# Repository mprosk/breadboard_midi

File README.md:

# MIDI Breadboard Adapter
MIDI breakout board for prototyping on a breadboard. Easily communicate with digital instruments from an Arduino or other microcontroller. Includes all hardware required to drive the MIDI current loop from a UART.

## Voltage Compatibility

The breakout board can be configured to work with both 3.3V and 5V microcontrollers. Since MIDI uses current, not voltage to encode bits, the values of the current limiting resistors can be changed to reflect the different voltage level. The list of resistor values for each voltage mode is shown below.

| Resistor | 5V Bus | 3.3V Bus |
| -------- | ------ | -------- |
| R1       | 280    | 180      |
| R2       | 220    | 220      |
| R3       | 220    | 10       |
| R4       | 220    | 33       |

## MIDI Pass Through

The adapter can also be configured to pass the MIDI IN data that it receives directly to the MIDI OUT stream, allowing your microcontroller to passively monitor the MIDI link between two other MIDI devices. Useful for debugging or for splitting the upstream data to both your project and another MIDI endpoint.

To enable this option, simply connect a jumper between the IN and OUT pins on the breadboard adapter.

## Bill of Materials

| Quantity | Line Item                                          |
| -------- | -------------------------------------------------- |
| 1        | 6N138 optoisolator                                 |
| 1        | 8DIP socket                                        |
| 1        | 1N914 signal diode                                 |
| 2        | 5-pin 180' DIN socket                              |
| 3        | 0.1uF capacitors                                   |
| 1        | 74LVCG125 buffer gate                              |
| 16       | 0.1" pitch male pin headers (4x 2-unit, 2x 4-unit) |

#### 5V Configuration

| Quantity | Line Item         |
| -------- | ----------------- |
| 3        | 220 ohm resistors |
| 1        | 280 ohm resistor  |

#### 3.3V Configuration

| Quantity | Line Item        |
| -------- | ---------------- |
| 1        | 10 ohm resistor  |
| 1        | 33 ohm resistor  |
| 1        | 220 ohm resistor |
| 1        | 280 ohm resistor |

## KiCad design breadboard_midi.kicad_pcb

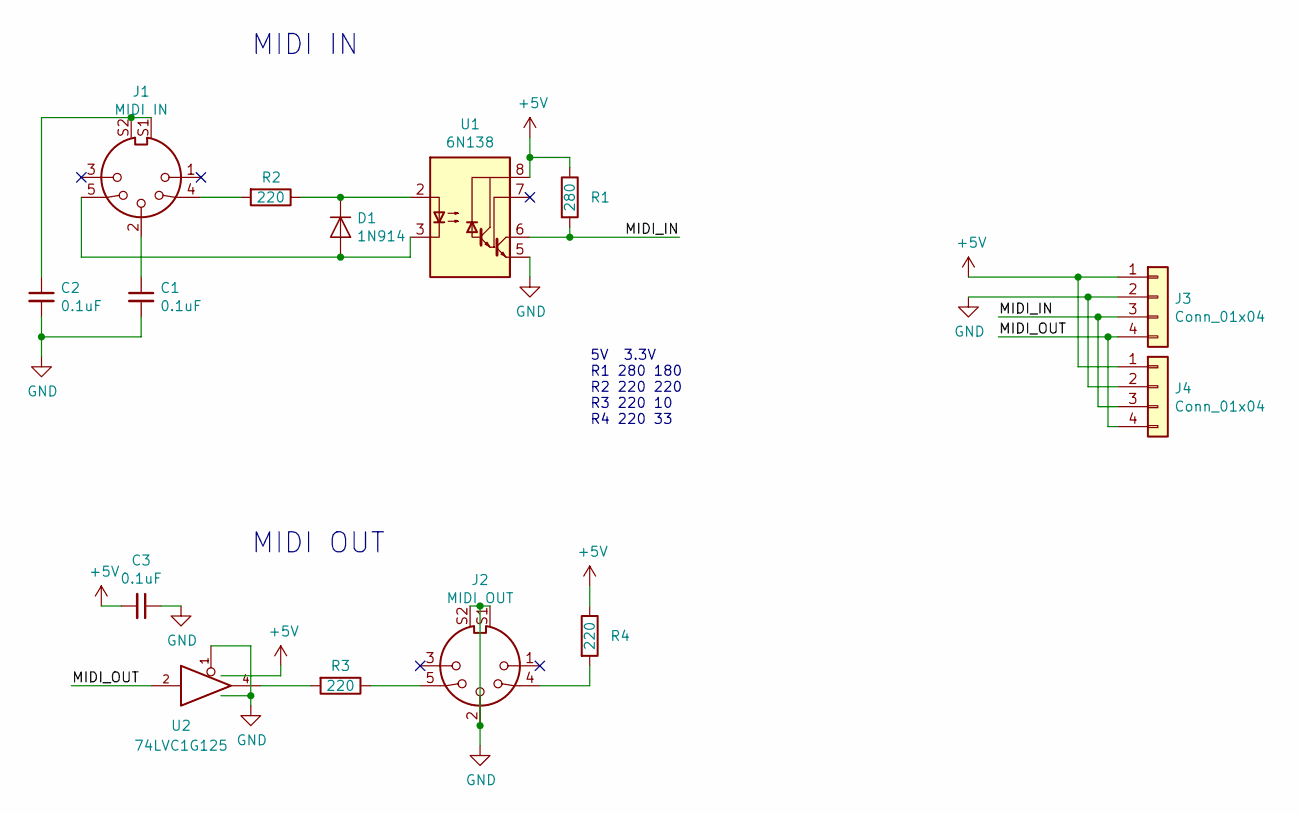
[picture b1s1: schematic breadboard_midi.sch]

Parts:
C1, C2, C3: 0.1uF; C_Disc_D3.0mm_W1.6mm_P2.50mm
D1: 1N914; D_DO-35_SOD27_P7.62mm_Horizontal
J1: MIDI IN; CUI_SDS-50J
J2: MIDI OUT; CUI_SDS-50J
J3, J4: Conn_01x04; PinHeader_1x04_P2.54mm_Vertical
R1: 280; R_Axial_DIN0207_L6.3mm_D2.5mm_P10.16mm_Horizontal
R2, R3, R4: 220; R_Axial_DIN0207_L6.3mm_D2.5mm_P10.16mm_Horizontal
U1: 6N138; DIP-8_W7.62mm_Socket
U2: 74LVC1G125; SOT-23-5_HandSoldering

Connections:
+5V: C3.2, J3.1, J4.1, R1.1, R4.1, U1.8 (VCC), U2.5 (VCC)
/MIDI_IN: J3.3, J4.3, R1.2, U1.6 (VO2)
/MIDI_OUT: J3.4, J4.4, U2.2
GND: C1.2, C2.2, C3.1, J2.2, J2.S1, J2.S2, J3.2, J4.2, U1.5 (GND), U2.1, U2.3 (GND)
unnamed: C1.1, J1.2
unnamed: C2.1, J1.S1, J1.S2
unnamed: D1.1 (K), R2.1, U1.2 (C1)
unnamed: D1.2 (A), J1.5, U1.3 (C2)
unnamed: J1.4, R2.2
unnamed: J2.4, R4.2
unnamed: J2.5, R3.1
unnamed: R3.2, U2.4

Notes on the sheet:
MIDI OUT
MIDI IN
5V 3.3V R1 280 180 R2 220 220 R3 220 10 R4 220 33

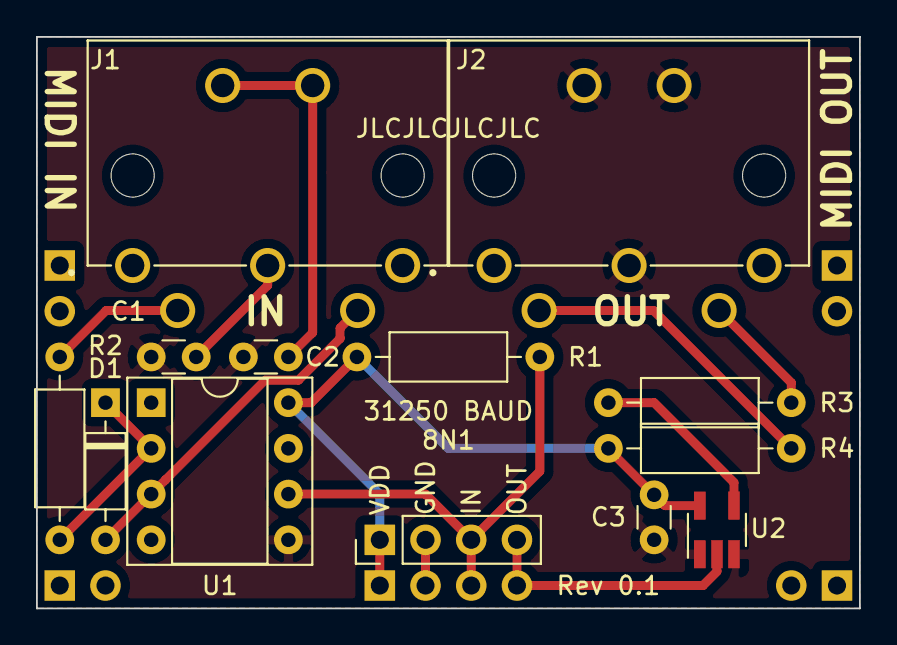
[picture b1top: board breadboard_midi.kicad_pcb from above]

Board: 2 copper layers, 45.7 x 31.8 mm, 14 parts (1 on the bottom side), 12 nets.

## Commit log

2020-09-09 Add KiCAD files
2020-09-10 Tweak schematic more
2020-09-10 Refresh file exports
2020-09-10 Move PCB files to separate folder
2020-09-10 Update gerber zip
2020-09-10 Update ReADME'
2020-12-23 Refresh Gerber files
